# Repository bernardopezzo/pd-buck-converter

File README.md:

# USB-C PD Sink & Synchronous Buck Converter (CH224K + SY8303AIC)

An all-in-one compact hardware module combining a **USB Type-C Power Delivery (PD) Sink Controller** and a **3A Synchronous Step-Down (Buck) DC-DC Converter**. 

Designed in **KiCad 10** using standard JLCPCB SMT components for direct, low-cost assembly.

Please verify the design before using, it is not finished and was not tested.

---

## 📖 Overview & Architecture

Modern USB-C chargers (USB-PD / QC adapters) can supply up to 20V at high currents, but most embedded microcontrollers, sensors, and development boards require lower voltages (such as 3.3V, 5V, or 12V).

This board integrates two stages onto a single PCB:
1. **USB-PD Sink Trigger (WCH CH224K)**: Negotiates high-voltage power profiles (`5V`, `9V`, `12V`, `15V`, or `20V`) from any standard USB-C PD power supply using a 3-position onboard DIP switch.
2. **Synchronous Buck Converter (Silergy SY8303AIC)**: Steps down the negotiated input voltage to an adjustable regulated DC output capable of delivering up to **3A continuous current** with high efficiency and minimal thermal dissipation.

```
                     ┌──────────────────┐
                     │ USB-C Connector  │
                     │  (TYPE-C-31-M-12)│
                     └────────┬─────────┘
                              │ VBUS (5V - 20V)
             ┌────────────────┴────────────────┐
             │                                 │
             ▼                                 ▼
   ┌────────────────────┐            ┌────────────────────┐
   │    WCH CH224K      │            │  Silergy SY8303AIC │
   │ USB-PD Controller  │            │ 3A Step-Down Buck  │
   └─────────┬──────────┘            └─────────┬──────────┘
             │                                 │
     [3-Pos DIP Switch]                        ▼
     Configures Request             Adjustable Output VOUT
     (5V/9V/12V/15V/20V)               via Trimmer (R6)
```

---

## ⚡ Technical Specifications

| Parameter | Specification |
|---|---|
| **Input Connector** | 16-Pin USB Type-C (Receptacle, SMT) |
| **Supported PD Profiles** | 5V, 9V, 12V, 15V, 20V (DIP switch selectable) |
| **PD Controller IC** | WCH CH224K (ESSOP-10) |
| **Buck Converter IC** | Silergy SY8303AIC (TSOT-23-8) |
| **Converter Topology** | High-efficiency synchronous rectification buck |
| **Maximum Output Current** | 3.0 A continuous |
| **Switching Frequency** | Up to 2.5 MHz (compact inductor footprint) |
| **Output Voltage Regulation**| Adjustable via 100kΩ precision potentiometer (R6) |
| **Passives Footprints** | 0603 (Resistors/Capacitors), 0805 & 1206 (Bulk MLCC) |
| **Self-Contained Libraries** | Includes complete 3D models (`.step`, `.wrl`) and symbols |

---

## 🎛️ DIP Switch Configuration (CH224K Voltage Selection)

The onboard 3-position DIP switch (`U2`, `SMXMS-03K-TP`) interfaces directly with the `CFG1`, `CFG2`, and `CFG3` pins of the CH224K controller to request the desired USB-PD power profile (check before applying):

| Desired VBUS | SW1 (CFG1) | SW2 (CFG2) | SW3 (CFG3) | Notes |
|:---:|:---:|:---:|:---:|---|
| **5V** | OFF | OFF | OFF | Default USB standard safe profile |
| **9V** | ON | OFF | OFF | Common for fast charging |
| **12V** | ON | ON | OFF | Ideal for 12V LED strips, relays & routers |
| **15V** | ON | ON | ON | Specialized audio/DSP supply |
| **20V** | OFF | ON | ON | Maximum PD power profile (up to 60W–100W) |

> **Note:** If the connected USB-C power supply does not support the requested profile, the CH224K automatically falls back to the nearest lower voltage profile supported by the adapter.

---

## 📋 Bill of Materials (BOM)

All components are standard parts readily available in the **JLCPCB / LCSC** SMT catalog:

| Designator | Qty | Value / Component | Package / Footprint | LCSC Part # | Description |
|---|---|---|---|---|---|
| **U1** | 1 | CH224K | ESSOP-10-150mil-1mm | `C970725` | USB-PD 3.0 sink power receiver controller |
| **U3** | 1 | SY8303AIC | TSOT-23-8 | `C97054` | 4.5V–40V, 3A synchronous step-down buck converter |
| **U2** | 1 | DIP-Switch (3-Pos) | SMXMS-03K-TP (P=1.27mm) | `C5439770` | 3-position SMD DIP switch |
| **USBC1** | 1 | USB Type-C Receptacle | TYPE-C-31-M-12 (16-Pin) | `C165948` | USB 2.0 / PD 20V 5A right-angle receptacle |
| **L1** | 1 | 3.3 µH | SLO0530H3R3MTT (5.4x5.2mm)| `C325963` | 5.5A / 28mΩ molded power inductor |
| **R6** | 1 | 100 kΩ Potentiometer | ST-32EA (SMD Trimmer) | `C132894` | Precision variable potentiometer for output tuning |
| **C2, C3** | 2 | 10 µF | 1206 (X7R, 50V) | `C89632` | High-voltage input ceramic decoupling capacitors |
| **C4, C5** | 2 | 22 µF | 0805 (X5R, 25V) | `C129303` | Low-ESR output smoothing capacitors |
| **C1, C6** | 2 | 100 nF | 0603 (X7R, 50V) | `C14663` | High-frequency IC bypass decoupling capacitors |
| **R1, R3, R4, R5** | 4 | 10 kΩ | 0603 (±1%) | `C25804` | Bias and pull-up configuration resistors |
| **R7, R8** | 2 | 5.1 kΩ | 0603 (±1%) | `C23186` | USB Type-C CC1 / CC2 detection pull-downs |
| **R2** | 1 | 1 kΩ | 0603 (±1%) | `C21190` | Feedback loop divider base resistor |
| **R9** | 1 | 100 kΩ | 0603 (±1%) | `C25803` | Auxiliary feedback / pull-down resistor |

---

## 📁 Repository Structure

```
pd-buck-converter/
├── PD_Buck.kicad_pro       # KiCad 10 main project configuration
├── PD_Buck.kicad_sch       # Complete schematic with design annotations
├── PD_Buck.kicad_pcb       # Two-layer PCB layout with routing and power copper pours
├── sym-lib-table           # Portable symbol library table (${KIPRJMOD} relative paths)
├── fp-lib-table            # Portable footprint library table (${KIPRJMOD} relative paths)
├── JLCImport.kicad_sym     # Self-contained KiCad symbol library for all BOM parts
├── JLCImport.pretty/       # KiCad footprint files (.kicad_mod)
├── JLCImport.3dshapes/     # 3D models (.step and .wrl) for 3D viewer rendering
├── .gitignore              # Ignores lock files (*.lck), backups (*.bak), and autosaves
└── README.md               # Detailed documentation, BOM, and hardware specs
```

> **Zero Missing Libraries**: All schematic symbols, footprints, and 3D shapes are contained locally in the repository using KiCad's `${KIPRJMOD}` path variable. It opens cleanly out-of-the-box on any computer without missing symbol or footprint warnings.

---

## 🛠️ How to Open & Modify in KiCad

1. Clone or download this repository.
2. Launch **KiCad 10** (or later).
3. Select **File > Open Project** and navigate to `PD_Buck.kicad_pro`.
4. Open the Schematic Editor (`PD_Buck.kicad_sch`) or the PCB Editor (`PD_Buck.kicad_pcb`).
5. In the PCB Editor, press `Alt + 3` to open the 3D Viewer and view the fully rendered 3D board assembly.

---

## 🏭 Manufacturing & Fabrication (JLCPCB Guide)

To order assembled boards from JLCPCB:
1. **Gerbers & Drill**:
   - In KiCad PCB Editor, click **File > Fabrication Outputs > Gerbers (.gbr)**.
   - Click **Plot**, then click **Generate Drill Files**.
   - Zip all resulting `.gbr` and `.drl` files together.
2. **BOM & CPL (Pick & Place)**:
   - Use KiCad's built-in export or the `kicad-jlcpcb-tools` plugin to generate `BOM.csv` and `CPL.csv` (positions).
   - All components in this project have pre-assigned LCSC part numbers matching the JLCPCB SMT parts library.

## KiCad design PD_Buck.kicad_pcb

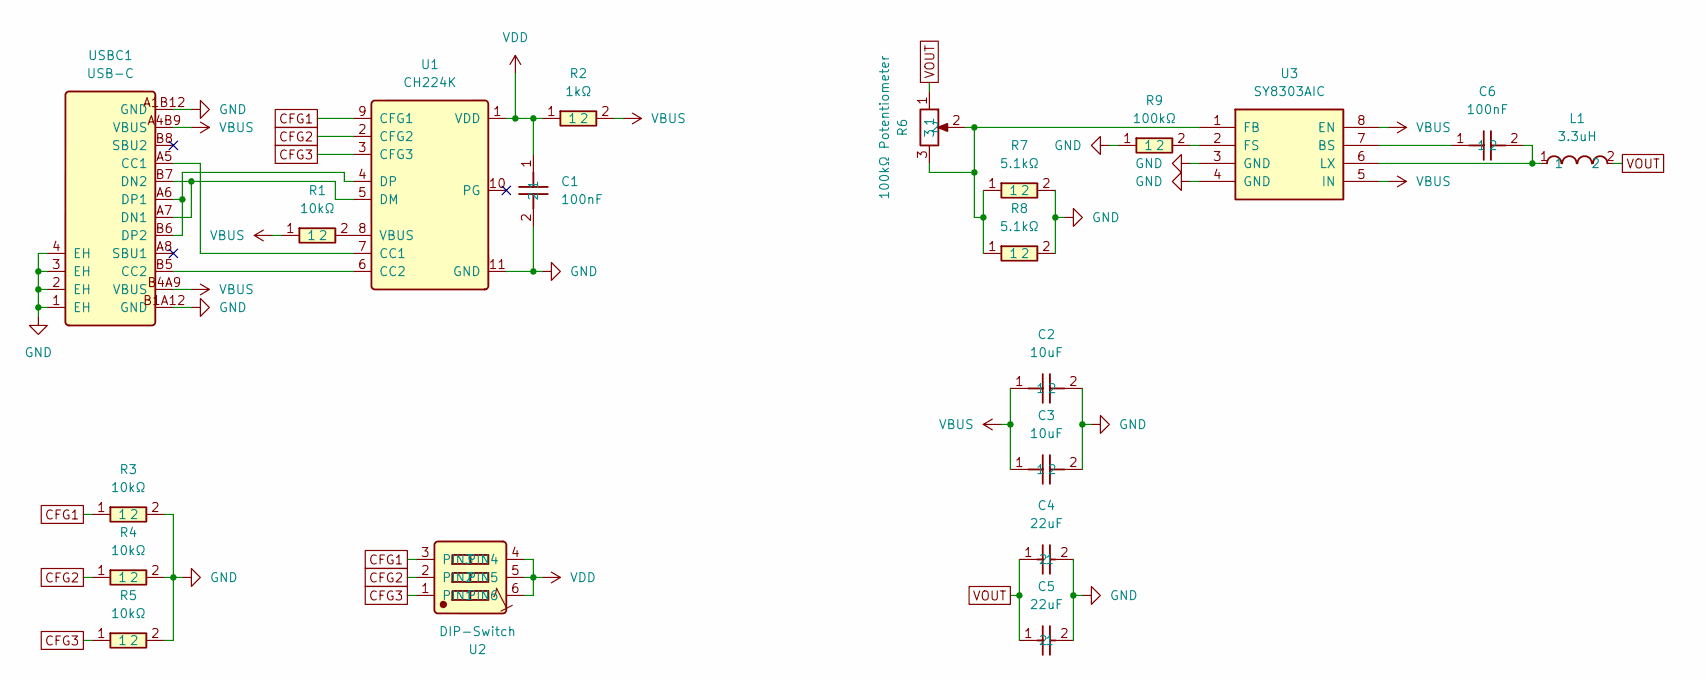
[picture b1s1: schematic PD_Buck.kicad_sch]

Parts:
C1, C6: 100nF; CC0603KRX7R9BB104; Manufacturer Part CC0603KRX7R9BB104; LCSC C14663
C2, C3: 10uF; CL31B106KBHNNNE; Manufacturer Part CL31B106KBHNNNE; LCSC C89632
C4, C5: 22uF; 0805X226M250NT; Manufacturer Part 0805X226M250NT; LCSC C129303
L1: 3.3uH; SLO0530H3R3MTT; Manufacturer Part SLO0530H3R3MTT; LCSC C325963
R1, R3, R4, R5: 10kΩ; 0603WAF1002T5E; Manufacturer Part 0603WAF1002T5E; LCSC C25804
R2: 1kΩ; 0603WAF1001T5E; Manufacturer Part 0603WAF1001T5E; LCSC C21190
R6: 100kΩ Potentiometer; ST-32EA_100K_ohm_104; Manufacturer Part ST-32EA 100K ohm (104); LCSC C132894
R7, R8: 5.1kΩ; 0603WAF5101T5E; Manufacturer Part 0603WAF5101T5E; LCSC C23186
R9: 100kΩ; 0603WAF1003T5E; Manufacturer Part 0603WAF1003T5E; LCSC C25803
U1: CH224K; Manufacturer Part CH224K; LCSC C970725
U2: DIP-Switch; SMXMS-03K-TP; Manufacturer Part SMXMS-03K-TP; LCSC C5439770
U3: SY8303AIC; Manufacturer Part SY8303AIC; LCSC C97054
USBC1: USB-C; TYPE-C-31-M-12; Manufacturer Part TYPE-C-31-M-12; LCSC C165948

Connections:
CFG1: R3.1, U1.9 (CFG1), U2.3 (PIN3)
CFG2: R4.1, U1.2 (CFG2), U2.2 (PIN2)
CFG3: R5.1, U1.3 (CFG3), U2.1 (PIN1)
GND: C1.2, C2.2, C3.2, C4.2, C5.2, R3.2, R4.2, R5.2, R7.2, R8.2, R9.1, U1.11 (GND), U3.3 (GND), U3.4 (GND), USBC1.1 (EH), USBC1.2 (EH), USBC1.3 (EH), USBC1.4 (EH), USBC1.A1B12 (GND), USBC1.B1A12 (GND)
unnamed: U1.7 (CC1), USBC1.A5 (CC1)
unnamed: U1.6 (CC2), USBC1.B5 (CC2)
unnamed: U1.5 (DM), USBC1.A7 (DN1), USBC1.B7 (DN2)
unnamed: U1.4 (DP), USBC1.A6 (DP1), USBC1.B6 (DP2)
unnamed: R1.2, U1.8 (VBUS)
unnamed: C6.1, U3.7 (BS)
unnamed: R6.2, R6.3, R7.1, R8.1, U3.1 (FB)
unnamed: R9.2, U3.2 (FS)
unnamed: C6.2, L1.1, U3.6 (LX)
VBUS: C2.1, C3.1, R1.1, R2.2, U3.5 (IN), U3.8 (EN), USBC1.A4B9 (VBUS), USBC1.B4A9 (VBUS)
VDD: C1.1, R2.1, U1.1 (VDD), U2.4 (PIN4), U2.5 (PIN5), U2.6 (PIN6)
VOUT: C4.1, C5.1, L1.2, R6.1

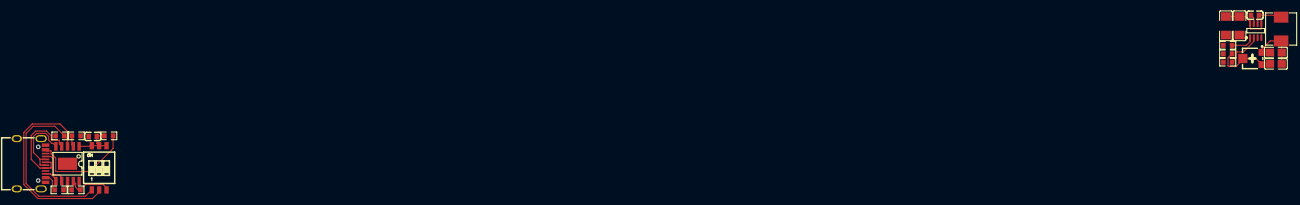
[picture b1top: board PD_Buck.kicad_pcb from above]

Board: 2 copper layers, 20 parts (0 on the bottom side), 16 nets.
